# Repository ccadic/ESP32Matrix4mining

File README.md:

# ESP32Matrix4mining
Prototype of a multi ESP32S3 board for mining purpose
GPL3

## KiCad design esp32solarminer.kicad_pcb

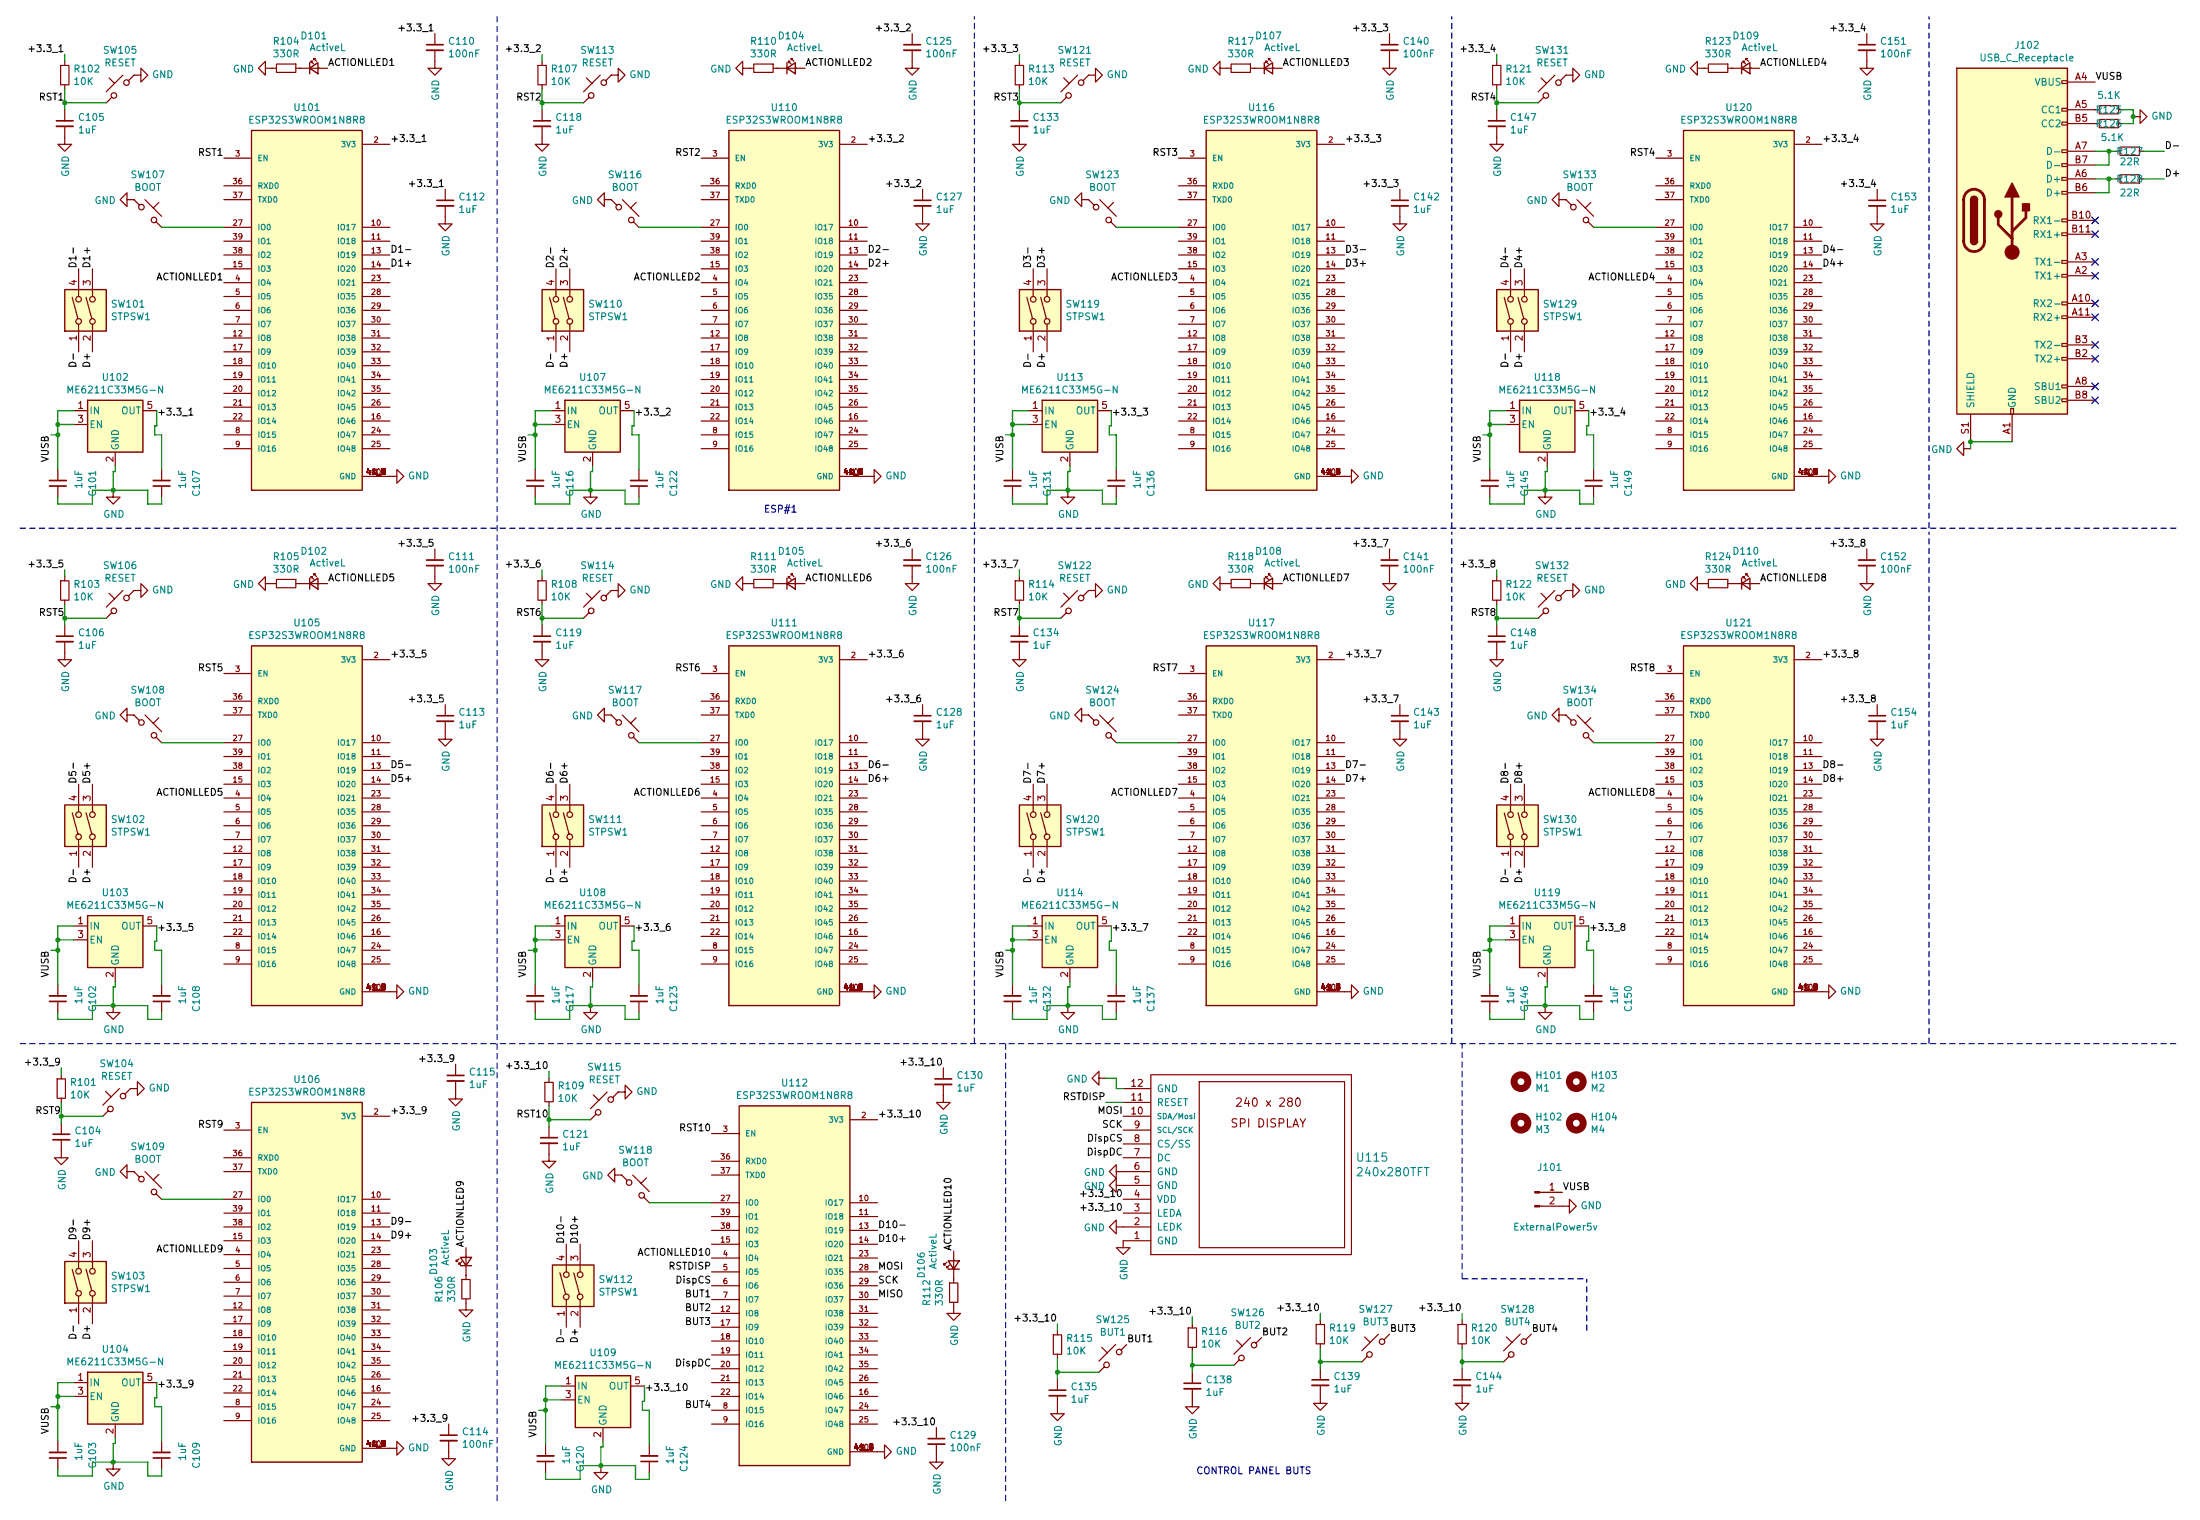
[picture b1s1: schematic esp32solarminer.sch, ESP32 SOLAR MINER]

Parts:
C101, C102, C103, C107, C108, C109, C116, C117, C120, C122, C123, C124, C131, C132, C136, C137, C145, C146, C149, C150: 1uF; C_0603_1608Metric; LCSC C83063
C104, C105, C106, C112, C113, C115, C118, C119, C121, C127, C128, C130, C133, C134, C135, C138, C139, C142, C143, C144, C147, C148, C153, C154: 1uF; C_0603_1608Metric
C110, C111, C114, C125, C126, C129, C140, C141, C151, C152: 100nF; C_0603_1608Metric
D101, D102, D103, D104, D105, D106, D107, D108, D109, D110: ActiveL; LED_0603_1608Metric
H101: M1; MountingHole_4.5mm
H102: M3; MountingHole_4.5mm
H103: M2; MountingHole_4.5mm
H104: M4; MountingHole_4.5mm
J101: ExternalPower5v; TerminalBlock_bornier-2_P5.08mm
J102: USB_C_Receptacle; GT-USB-7010
R101, R102, R103, R107, R108, R109, R113, R114, R115, R116, R119, R120, R121, R122: 10K; R_0603_1608Metric
R104, R105, R106, R110, R111, R112, R117, R118, R123, R124: 330R; R_0603_1608Metric
R125, R126: 5.1K; R_0603_1608Metric
R127, R128: 22R; R_0603_1608Metric
SW101, SW102, SW103, SW110, SW111, SW112, SW119, SW120, SW129, SW130: STPSW1; SW_DIP_SPSTx02_Slide_9.78x7.26mm_W8.61mm_P2.54mm
SW104, SW105, SW106, SW113, SW114, SW115, SW121, SW122, SW131, SW132: RESET; SKRPABE010
SW107, SW108, SW109, SW116, SW117, SW118, SW123, SW124, SW133, SW134: BOOT; SKRPABE010
SW125: BUT1; SKRPABE010
SW126: BUT2; SKRPABE010
SW127: BUT3; SKRPABE010
SW128: BUT4; SKRPABE010
U101, U105, U106, U110, U111, U112, U116, U117, U120, U121: ESP32S3WROOM1N8R8; XCVR_ESP32S3WROOM1N8R8; PARTREV v1.0
U102, U103, U104, U107, U108, U109, U113, U114, U118, U119: ME6211C33M5G-N; SOT-23-5; LCSC C485517
U115: 240x280TFT; 240240TFT

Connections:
/+3.3_1: C107.2, C110.1, C112.1, R102.1, U101.2 (3V3), U102.5 (OUT)
/+3.3_2: C122.2, C125.1, C127.1, R107.1, U107.5 (OUT), U110.2 (3V3)
/+3.3_3: C136.2, C140.1, C142.1, R113.1, U113.5 (OUT), U116.2 (3V3)
/+3.3_4: C149.2, C151.1, C153.1, R121.1, U118.5 (OUT), U120.2 (3V3)
/+3.3_5: C108.2, C111.1, C113.1, R103.1, U103.5 (OUT), U105.2 (3V3)
/+3.3_6: C123.2, C126.1, C128.1, R108.1, U108.5 (OUT), U111.2 (3V3)
/+3.3_7: C137.2, C141.1, C143.1, R114.1, U114.5 (OUT), U117.2 (3V3)
/+3.3_8: C150.2, C152.1, C154.1, R122.1, U119.5 (OUT), U121.2 (3V3)
/+3.3_9: C109.2, C114.1, C115.1, R101.1, U104.5 (OUT), U106.2 (3V3)
/+3.3_10: C124.2, C129.1, C130.1, R109.1, R115.1, R116.1, R119.1, R120.1, U109.5 (OUT), U112.2 (3V3), U115.3 (LEDA), U115.4 (VDD)
/ACTIONLLED1: D101.2 (A), U101.4 (IO4)
/ACTIONLLED2: D104.2 (A), U110.4 (IO4)
/ACTIONLLED3: D107.2 (A), U116.4 (IO4)
/ACTIONLLED4: D109.2 (A), U120.4 (IO4)
/ACTIONLLED5: D102.2 (A), U105.4 (IO4)
/ACTIONLLED6: D105.2 (A), U111.4 (IO4)
/ACTIONLLED7: D108.2 (A), U117.4 (IO4)
/ACTIONLLED8: D110.2 (A), U121.4 (IO4)
/ACTIONLLED9: D103.2 (A), U106.4 (IO4)
/ACTIONLLED10: D106.2 (A), U112.4 (IO4)
/BUT1: SW125.1, U112.7 (IO7)
/BUT2: SW126.1, U112.12 (IO8)
/BUT3: SW127.1, U112.17 (IO9)
/BUT4: SW128.1, U112.8 (IO15)
/D1+: SW101.3, U101.14 (IO20)
/D1-: SW101.4, U101.13 (IO19)
/D2+: SW110.3, U110.14 (IO20)
/D2-: SW110.4, U110.13 (IO19)
/D3+: SW119.3, U116.14 (IO20)
/D3-: SW119.4, U116.13 (IO19)
/D4+: SW129.3, U120.14 (IO20)
/D4-: SW129.4, U120.13 (IO19)
/D5+: SW102.3, U105.14 (IO20)
/D5-: SW102.4, U105.13 (IO19)
/D6+: SW111.3, U111.14 (IO20)
/D6-: SW111.4, U111.13 (IO19)
/D7+: SW120.3, U117.14 (IO20)
/D7-: SW120.4, U117.13 (IO19)
/D8+: SW130.3, U121.14 (IO20)
/D8-: SW130.4, U121.13 (IO19)
/D9+: SW103.3, U106.14 (IO20)
/D9-: SW103.4, U106.13 (IO19)
/D10+: SW112.3, U112.14 (IO20)
/D10-: SW112.4, U112.13 (IO19)
/D+: R128.1, SW101.2, SW102.2, SW103.2, SW110.2, SW111.2, SW112.2, SW119.2, SW120.2, SW129.2, SW130.2
/D-: R127.1, SW101.1, SW102.1, SW103.1, SW110.1, SW111.1, SW112.1, SW119.1, SW120.1, SW129.1, SW130.1
/DispCS: U112.6 (IO6), U115.8 (CS/SS)
/DispDC: U112.20 (IO12), U115.7 (DC)
/MOSI: U112.28 (IO35), U115.10 (SDA/Mosi)
/RST1: C105.1, R102.2, SW105.2, U101.3 (EN)
/RST2: C118.1, R107.2, SW113.2, U110.3 (EN)
/RST3: C133.1, R113.2, SW121.2, U116.3 (EN)
/RST4: C147.1, R121.2, SW131.2, U120.3 (EN)
/RST5: C106.1, R103.2, SW106.2, U105.3 (EN)
/RST6: C119.1, R108.2, SW114.2, U111.3 (EN)
/RST7: C134.1, R114.2, SW122.2, U117.3 (EN)
/RST8: C148.1, R122.2, SW132.2, U121.3 (EN)
/RST9: C104.1, R101.2, SW104.2, U106.3 (EN)
/RST10: C121.1, R109.2, SW115.2, U112.3 (EN)
/RSTDISP: U112.5 (IO5), U115.11 (RESET)
/SCK: U112.29 (IO36), U115.9 (SCL/SCK)
/VUSB: C101.2, C102.2, C103.2, C116.2, C117.2, C120.2, C131.2, C132.2, C145.2, C146.2, J101.1, J102.A4 (VBUS), J102.A9 (VBUS), J102.B4 (VBUS), J102.B9 (VBUS), U102.1 (IN), U102.3 (EN), U103.1 (IN), U103.3 (EN), U104.1 (IN), U104.3 (EN), U107.1 (IN), U107.3 (EN), U108.1 (IN), U108.3 (EN), U109.1 (IN), U109.3 (EN), U113.1 (IN), U113.3 (EN), U114.1 (IN), U114.3 (EN), U118.1 (IN), U118.3 (EN), U119.1 (IN), U119.3 (EN)
GND: C101.1, C102.1, C103.1, C104.2, C105.2, C106.2, C107.1, C108.1, C109.1, C110.2, C111.2, C112.2, C113.2, C114.2, C115.2, C116.1, C117.1, C118.2, C119.2, C120.1, C121.2, C122.1, C123.1, C124.1, C125.2, C126.2, C127.2, C128.2, C129.2, C130.2, C131.1, C132.1, C133.2, C134.2, C135.2, C136.1, C137.1, C138.2, C139.2, C140.2, C141.2, C142.2, C143.2, C144.2, C145.1, C146.1, C147.2, C148.2, C149.1, C150.1, C151.2, C152.2, C153.2, C154.2, J101.2, J102.A1 (GND), J102.A12 (GND), J102.B1 (GND), J102.B12 (GND), J102.S1 (SHIELD), R104.2, R105.2, R106.2, R110.2, R111.2, R112.2, R117.2, R118.2, R123.2, R124.2, R125.1, R126.1, SW104.1, SW105.1, SW106.1, SW107.1, SW108.1, SW109.1, SW113.1, SW114.1, SW115.1, SW116.1, SW117.1, SW118.1, SW121.1, SW122.1, SW123.1, SW124.1, SW131.1, SW132.1, SW133.1, SW134.1, U101.1 (GND), U101.40 (GND), U101.41_1 (GND), U101.41_2 (GND), U101.41_3 (GND), U101.41_4 (GND), U101.41_5 (GND), U101.41_6 (GND), U101.41_7 (GND), U101.41_8 (GND), U101.41_9 (GND), U102.2 (GND), U103.2 (GND), U104.2 (GND), U105.1 (GND), U105.40 (GND), U105.41_1 (GND), U105.41_2 (GND), U105.41_3 (GND), U105.41_4 (GND), U105.41_5 (GND), U105.41_6 (GND), U105.41_7 (GND), U105.41_8 (GND), U105.41_9 (GND), U106.1 (GND), U106.40 (GND), U106.41_1 (GND), U106.41_2 (GND), U106.41_3 (GND), U106.41_4 (GND), U106.41_5 (GND), U106.41_6 (GND), U106.41_7 (GND), U106.41_8 (GND), U106.41_9 (GND), U107.2 (GND), U108.2 (GND), U109.2 (GND), U110.1 (GND), U110.40 (GND), U110.41_1 (GND), U110.41_2 (GND), U110.41_3 (GND), U110.41_4 (GND), U110.41_5 (GND), U110.41_6 (GND), U110.41_7 (GND), U110.41_8 (GND), U110.41_9 (GND), U111.1 (GND), U111.40 (GND), U111.41_1 (GND), U111.41_2 (GND), U111.41_3 (GND), U111.41_4 (GND), U111.41_5 (GND), U111.41_6 (GND), U111.41_7 (GND), U111.41_8 (GND), U111.41_9 (GND), U112.1 (GND), U112.40 (GND), U112.41_1 (GND), U112.41_2 (GND), U112.41_3 (GND), U112.41_4 (GND), U112.41_5 (GND), U112.41_6 (GND), U112.41_7 (GND), U112.41_8 (GND), U112.41_9 (GND), U113.2 (GND), U114.2 (GND), U115.1 (GND), U115.2 (LEDK), U115.5 (GND), U115.6 (GND), U115.12 (GND), U116.1 (GND), U116.40 (GND), U116.41_1 (GND), U116.41_2 (GND), U116.41_3 (GND), U116.41_4 (GND), U116.41_5 (GND), U116.41_6 (GND), U116.41_7 (GND), U116.41_8 (GND), U116.41_9 (GND), U117.1 (GND), U117.40 (GND), U117.41_1 (GND), U117.41_2 (GND), U117.41_3 (GND), U117.41_4 (GND), U117.41_5 (GND), U117.41_6 (GND), U117.41_7 (GND), U117.41_8 (GND), U117.41_9 (GND), U118.2 (GND), U119.2 (GND), U120.1 (GND), U120.40 (GND), U120.41_1 (GND), U120.41_2 (GND), U120.41_3 (GND), U120.41_4 (GND), U120.41_5 (GND), U120.41_6 (GND), U120.41_7 (GND), U120.41_8 (GND), U120.41_9 (GND), U121.1 (GND), U121.40 (GND), U121.41_1 (GND), U121.41_2 (GND), U121.41_3 (GND), U121.41_4 (GND), U121.41_5 (GND), U121.41_6 (GND), U121.41_7 (GND), U121.41_8 (GND), U121.41_9 (GND)
unnamed: C135.1, R115.2, SW125.2
unnamed: C138.1, R116.2, SW126.2
unnamed: C139.1, R119.2, SW127.2
unnamed: C144.1, R120.2, SW128.2
unnamed: D101.1 (K), R104.1
unnamed: D102.1 (K), R105.1
unnamed: D103.1 (K), R106.1
unnamed: D104.1 (K), R110.1
unnamed: D105.1 (K), R111.1
unnamed: D106.1 (K), R112.1
unnamed: D107.1 (K), R117.1
unnamed: D108.1 (K), R118.1
unnamed: D109.1 (K), R123.1
unnamed: D110.1 (K), R124.1
unnamed: J102.A5 (CC1), R125.2
unnamed: J102.A6 (D+), J102.B6 (D+), R128.2
unnamed: J102.A7 (D-), J102.B7 (D-), R127.2
unnamed: J102.B5 (CC2), R126.2
unnamed: SW107.2, U101.27 (IO0)
unnamed: SW108.2, U105.27 (IO0)
unnamed: SW109.2, U106.27 (IO0)
unnamed: SW116.2, U110.27 (IO0)
unnamed: SW117.2, U111.27 (IO0)
unnamed: SW118.2, U112.27 (IO0)
unnamed: SW123.2, U116.27 (IO0)
unnamed: SW124.2, U117.27 (IO0)
unnamed: SW133.2, U120.27 (IO0)
unnamed: SW134.2, U121.27 (IO0)

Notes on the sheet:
ESP#1
CONTROL PANEL BUTS

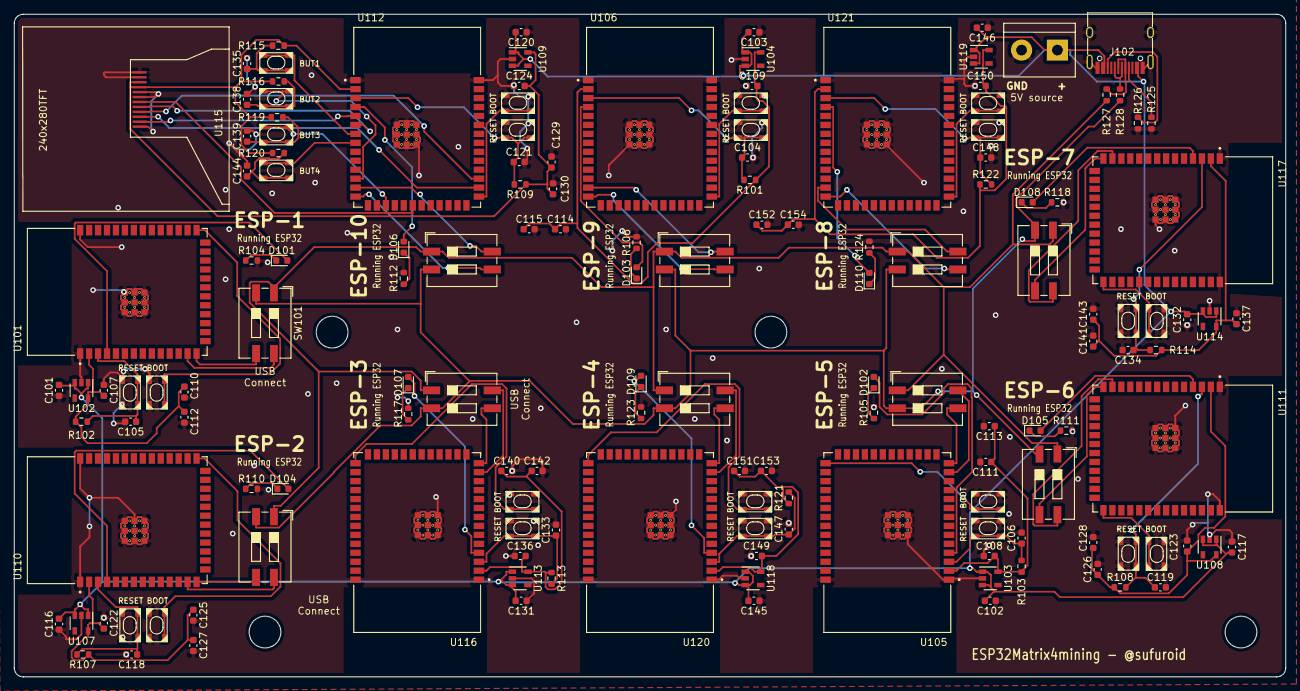
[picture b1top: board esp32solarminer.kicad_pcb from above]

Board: 2 copper layers, 180.3 x 94.0 mm, 153 parts (0 on the bottom side), 91 nets.
